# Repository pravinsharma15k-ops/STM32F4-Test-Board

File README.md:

# STM32F4 Test Board (REV2)

A compact STM32F405-based development board designed in **KiCad 10**. It has a 12 V screw-terminal power input, an on-board buck converter, USB micro-B, and standard debug and communication headers (SWD, I2C, UART).

## Features

- **MCU:** STM32F405RGT6 (ARM Cortex-M4, LQFP-64), 16 MHz crystal
- **Power input:** 12 V via 2-pin screw terminal, protected by a 250 mA fuse
- **Buck converter:** MP2359DJ-LF-Z (adjustable, feedback resistor divider)
- **USB:** micro-B connector with USBLC6-2SC6 ESD protection
- **Programming and debug:** 10-pin SWD header (SWCLK, SWDIO, SWO, NRST)
- **Communication:** I2C1 header (with 2.2 kOhm pull-ups) and USART3 header
- **User interface:** BOOT0 slide switch (BOOT / RUN), red power LED, blue status LED
- **Mounting:** four M3-style mounting holes with GND pads
- **Board:** 4-layer, rounded corners

## Board Preview

| 3D view (angled) | PCB layout |
|---|---|
|  |  |

## Schematic

The schematic has three sections:

1. **Connectors and USB**: power terminal, USB micro-B, SWD, I2C and UART headers
2. **Power circuitry**: MP2359 buck converter, inductor, diodes, ferrite bead for the analog supply
3. **STM32 microcontroller**: STM32F405RGT6, crystal, decoupling, BOOT0 and reset circuit

The PDF is in [`docs/STM32F4_REV2.pdf`](STM32F4_REV2/docs/STM32F4_REV2.pdf).

## Main Components

| Ref | Part | Purpose |
|---|---|---|
| U2 | STM32F405RGT6 | Main microcontroller |
| U1 | MP2359DJ-LF-Z | Buck converter |
| U3 | USBLC6-2SC6 | USB ESD protection |
| Q1 | AO3401A | P-channel MOSFET (power path) |
| D1, D2 | B5819W | Schottky diodes |
| D3 / D4 | Red LED / Blue LED | Power indicator / Status LED |
| Y1 | 16 MHz crystal | HSE clock |
| F1 | 250 mA fuse | Input protection |
| FB1 | 600 ohm @ 600 MHz ferrite bead | Analog supply filtering |
| L1, L2 | Inductors | Buck converter and filtering |
| SW1 | SPDT slide switch | BOOT0 select (BOOT / RUN) |
| J1 | Screw terminal 1x02 | 12 V power input |
| J2 | 2x5 header | SWD |
| J3 | 1x04 connector | I2C1 (SCL, SDA) |
| J4 | 1x04 connector | USART3 (TX, RX) |
| J6 | USB micro-B | USB data |
| H1-H4 | Mounting holes | Board mounting |

Full values are in the schematic and in the generated BOM.

## Repository Structure

```
.
├── STM32F4_REV2.kicad_pro      # KiCad project
├── STM32F4_REV2.kicad_sch      # Schematic
├── STM32F4_REV2.kicad_pcb      # PCB layout
STM32F4_REV2
├── libraries/                  # Custom symbols, footprints and 3D models
├── fabrication/                # Gerber, drill, BOM and position files
├── docs/                       # Schematic PDF, datasheets
├── images/  
└── README.md
```

## How to Open

1. Install [KiCad 10](https://www.kicad.org/download/).
2. Clone or download this repository.
3. Open `STM32F4_REV2.kicad_pro` in KiCad.
4. If KiCad shows missing symbol, footprint or 3D model errors, check **Preferences, Manage Symbol/Footprint Libraries** and **Configure Paths**, and point them to the `libraries/` folder.

## Fabrication

Production files are in `fabrication/`. To regenerate them in KiCad:

1. **PCB Editor, File, Fabrication Outputs, Gerbers (.gbr)**, then **Generate Drill Files**.
2. **File, Fabrication Outputs, Component Placement (.pos)** for assembly.
3. **Schematic Editor, Tools, Generate BOM** for the bill of materials.
4. Zip the Gerber and drill files and upload them to your PCB manufacturer.

Before ordering, run **ERC** in the schematic editor and **DRC** in the PCB editor, and make sure both show no errors.

## Status

- [x] Schematic complete
- [x] PCB layout and routing complete
- [x] 3D models assigned
- [ ] Board fabricated
- [ ] Board tested

## Credits

- Designed in [KiCad](https://www.kicad.org/) 10.
- Reference design and tutorial: Phil's Lab (YouTube), "KiCad STM32 + USB + Buck Converter PCB Design" (#11).
- MP2359 symbol/footprint and Molex connector 3D model from SnapMagic.

## Author

Pravin Kumar Sharma, ECE student.

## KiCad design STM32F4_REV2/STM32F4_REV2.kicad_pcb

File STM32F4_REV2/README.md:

# STM32F4 Test Board (REV2)

A compact STM32F405-based development board designed in **KiCad 10**. It has a 12 V screw-terminal power input, an on-board buck converter, USB micro-B, and standard debug and communication headers (SWD, I2C, UART).

## Features

- **MCU:** STM32F405RGT6 (ARM Cortex-M4, LQFP-64), 16 MHz crystal
- **Power input:** 12 V via 2-pin screw terminal, protected by a 250 mA fuse
- **Buck converter:** MP2359DJ-LF-Z (adjustable, feedback resistor divider)
- **USB:** micro-B connector with USBLC6-2SC6 ESD protection
- **Programming and debug:** 10-pin SWD header (SWCLK, SWDIO, SWO, NRST)
- **Communication:** I2C1 header (with 2.2 kOhm pull-ups) and USART3 header
- **User interface:** BOOT0 slide switch (BOOT / RUN), red power LED, blue status LED
- **Mounting:** four M3-style mounting holes with GND pads
- **Board:** 4-layer, rounded corners

## Board Preview

| 3D view (angled) | PCB layout |
|---|---|
|  |  |

## Schematic

The schematic has three sections:

1. **Connectors and USB**: power terminal, USB micro-B, SWD, I2C and UART headers
2. **Power circuitry**: MP2359 buck converter, inductor, diodes, ferrite bead for the analog supply
3. **STM32 microcontroller**: STM32F405RGT6, crystal, decoupling, BOOT0 and reset circuit

The PDF is in [`docs/STM32F4_REV2.pdf`](docs/STM32F4_REV2.pdf).

## Main Components

| Ref | Part | Purpose |
|---|---|---|
| U2 | STM32F405RGT6 | Main microcontroller |
| U1 | MP2359DJ-LF-Z | Buck converter |
| U3 | USBLC6-2SC6 | USB ESD protection |
| Q1 | AO3401A | P-channel MOSFET (power path) |
| D1, D2 | B5819W | Schottky diodes |
| D3 / D4 | Red LED / Blue LED | Power indicator / Status LED |
| Y1 | 16 MHz crystal | HSE clock |
| F1 | 250 mA fuse | Input protection |
| FB1 | 600 ohm @ 100 MHz ferrite bead | Analog supply filtering |
| L1, L2 | Inductors | Buck converter and filtering |
| SW1 | SPDT slide switch | BOOT0 select (BOOT / RUN) |
| J1 | Screw terminal 1x02 | 12 V power input |
| J2 | 2x5 header | SWD |
| J3 | 1x04 connector | I2C1 (SCL, SDA) |
| J4 | 1x04 connector | USART3 (TX, RX) |
| J6 | USB micro-B | USB data |
| H1-H4 | Mounting holes | Board mounting |

Full values are in the schematic and in the generated BOM.

## Repository Structure

```
.
├── STM32F4_REV2.kicad_pro      # KiCad project
├── STM32F4_REV2.kicad_sch      # Schematic
├── STM32F4_REV2.kicad_pcb      # PCB layout
├── libraries/                  # Custom symbols, footprints and 3D models
├── fabrication/                # Gerber, drill, BOM and position files
├── docs/                       # Schematic PDF, datasheets
├── images/                     # Screenshots used in this README
└── README.md
```

## How to Open

1. Install [KiCad 10](https://www.kicad.org/download/).
2. Clone or download this repository.
3. Open `STM32F4_REV2.kicad_pro` in KiCad.
4. If KiCad shows missing symbol, footprint or 3D model errors, check **Preferences, Manage Symbol/Footprint Libraries** and **Configure Paths**, and point them to the `libraries/` folder.

## Fabrication

Production files are in `fabrication/`. To regenerate them in KiCad:

1. **PCB Editor, File, Fabrication Outputs, Gerbers (.gbr)**, then **Generate Drill Files**.
2. **File, Fabrication Outputs, Component Placement (.pos)** for assembly.
3. **Schematic Editor, Tools, Generate BOM** for the bill of materials.
4. Zip the Gerber and drill files and upload them to your PCB manufacturer.

Before ordering, run **ERC** in the schematic editor and **DRC** in the PCB editor, and make sure both show no errors.

## Status

- [x] Schematic complete
- [x] PCB layout and routing complete
- [x] 3D models assigned
- [ ] Board fabricated
- [ ] Board tested

## Known Issues / To Do

- Silkscreen reads "STM32F4 TEXT BOARD", which should say "TEST BOARD".
- Verify all footprints against the exact parts being purchased, especially connectors.

## Credits

- Designed in [KiCad](https://www.kicad.org/) 10.
- Reference design and tutorial: Phil's Lab (YouTube), "KiCad STM32 + USB + Buck Converter PCB Design" (#11).
- MP2359 symbol/footprint and Molex connector 3D model from SnapMagic.

## License

Add a license of your choice (for example MIT for hardware files or CERN-OHL), and check the license of any reference design or library you reused.

## Author

Pravin Kumar Sharma, ECE student.

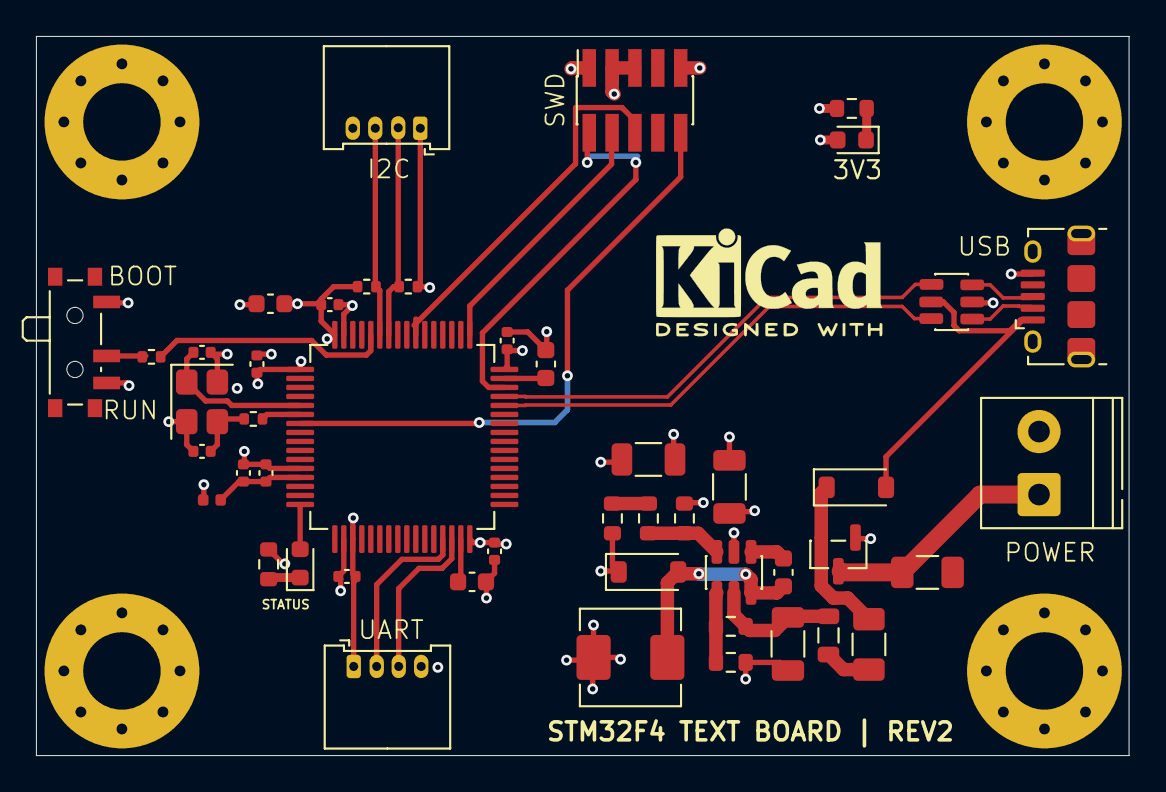
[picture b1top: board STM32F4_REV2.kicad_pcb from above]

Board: 4 copper layers, 60.7 x 40.0 mm, 51 parts (0 on the bottom side), 35 nets.

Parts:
C1, C2: 10u; C_1206_3216Metric
C3: 10U; C_1206_3216Metric
C4: 10n; C_0603_1608Metric
C5: 4u7; C_0603_1608Metric
C6, C7, C8, C9, C10: 100n; C_0402_1005Metric
C11: 1u; C_0402_1005Metric
C12: 10n; C_0402_1005Metric
C13, C14: 2u2; C_0603_1608Metric
C15, C16: 12p; C_0402_1005Metric
D1, D2: B5819W; D_SOD-123
D3: RED; LED_0603_1608Metric
D4: BLUE; LED_0603_1608Metric
F1, F1#2: 250mA; Fuse_1206_3216Metric
FB1: 600@ 600MHz; L_0805_2012Metric
H1, H2, H3, H4: MountingHole_Pad; MountingHole_4.3mm_M4_Pad_Via
J1: Screw_Terminal_01x02; TerminalBlock_Phoenix_PT-1,5-2-3.5-H_1x02_P3.50mm_Horizontal
J2: SWD; PinSocket_2x05_P1.27mm_Vertical_SMD
J3, J4: Conn_01x04; Molex_PicoBlade_53048-0410_1x04_P1.25mm_Horizontal
J6: USB_B_Micro; USB_Micro-B_Amphenol_10118194_Horizontal
L1: 10u; L_Sunlord_MWSA0518S
L2: 39n; L_0402_1005Metric
Q1: AO3401A; SOT-23
R1: 100k; R_0603_1608Metric
R2: 68k; R_0603_1608Metric
R3: 47k; R_0603_1608Metric
R4: 15k; R_0603_1608Metric
R5: 270; R_0603_1608Metric
R6: 1k; R_0603_1608Metric
R7: 10k; R_0402_1005Metric
R8: 47; R_0402_1005Metric
R9: 1k5; R_0603_1608Metric
R10, R11: 2k2; R_0402_1005Metric
SW1: SW_SPDT; SW_SPDT_PCM12
U1: MP2359DJ-LF-Z; SOT-23-6
U2: STM32F405RGT6; LQFP-64_10x10mm_P0.5mm
U3: USBLC6-2SC6; SOT-23-6
Y1: 16MHz; Crystal_SMD_3225-4Pin_3.2x2.5mm

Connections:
+3.3V: C2.2, C3.2, C5.1, C6.1, C7.1, C8.1, C9.1, C10.1, D3.2 (A), J2.1, J3.1, J4.1, L1.2, L2.1, R3.1, R10.1, R11.1, SW1.1 (A), U2.1 (VBAT), U2.19 (VDD), U2.32 (VDD), U2.48 (VDD), U2.64 (VDD)
+3.3VA: C11.1, C12.1, L2.2, U2.13 (VDDA)
+5V: D1.2 (A), J6.1 (VBUS), U3.5 (VBUS)
+12V: F1.1, J1.1, Q1.3 (D)
BOOTO: R7.1, U2.60 (BOOT0)
BUCK_BST: C4.2, U1.1 (BST)
BUCK_EN: R1.2, R2.1, U1.4 (EN)
BUCK_FB: R3.2, R4.1, U1.3 (FB)
BUCK_IN: C1.1, FB1.2, R1.1, U1.5 (IN)
BUCK_SW: C4.1, D2.2 (A), L1.1, U1.6 (SW)
GND: C1.2, C2.1, C3.1, C5.2, C6.2, C7.2, C8.2, C9.2, C10.2, C11.2, C12.2, C13.2, C14.2, C15.1, C16.2, D2.1 (K), H1.1 (1_1), H2.1 (1_1), H3.1 (1_1), H4.1 (1_1), J1.2, J2.3, J2.5, J2.9, J3.4, J4.4, J6.5 (GND), Q1.1 (G), R2.2, R5.2, R6.2, R9.2, SW1.3 (C), U1.2 (GND), U2.12 (VSSA), U2.18 (VSS), U2.63 (VSS), U3.2 (GND), Y1.2 (G), Y1.4 (G)
HSE_IN: C15.2, U2.5 (PH0), Y1.1
HSE_OUT: R8.1, U2.6 (PH1)
I2C1_SCL: J3.3, R11.2, U2.58 (PB6)
I2C1_SDA: J3.2, R10.2, U2.59 (PB7)
LED_STATUS: D4.2 (A), U2.16 (PA2)
NRST: J2.10, U2.7 (NRST)
unnamed: C16.1, R8.2, Y1.3
unnamed: D1.1 (K), F1#2.1, Q1.2 (S)
unnamed: D3.1 (K), R6.1
unnamed: D4.1 (K), R9.1
unnamed: F1#2.2, FB1.1
unnamed: R4.2, R5.1
unnamed: R7.2, SW1.2 (B)
unnamed: C13.1, U2.31 (VCAP_1)
unnamed: C14.1, U2.47 (VCAP_2)
SWCLK: J2.4, U2.49 (PA14)
SWDIO: J2.2, U2.46 (PA13)
SWO: J2.6, U2.55 (PB3)
USART3_RX: J4.2, U2.30 (PB11)
USART3_TX: J4.3, U2.29 (PB10)
USB_CONN_D+: J6.3 (D+), U3.3 (I/O2)
USB_CONN_D-: J6.2 (D-), U3.1 (I/O1)
USB_D+: U2.45 (PA12), U3.6 (I/O1)
USB_D-: U2.44 (PA11), U3.4 (I/O2)
